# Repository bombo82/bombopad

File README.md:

# BomboPad

BomboPad is an open-source, versatile 12-key macropad featuring dual rotary encoders and display support. Designed with
a focus on flexibility, it supports both wired and wireless configurations.

This repository contains the hardware design files, including electrical schematics and PCB layouts.

## Key Features

The current hardware version (**v0.3**) includes:

- **12 keys**: Designed for Kailh Choc v1 low-profile switches.
- **Dual Rotary Encoders**: Supports EC11 or EVQWGD001 encoders.
- **Display Support**: Compatible with SSD1306 128x32 OLED or Nice!View displays.
- **Microcontroller Compatibility**:
    - **Pro Micro** (or compatible) for wired builds.
        - **ATmega32U4**: Fully tested and regularly used.
        - **RP2040**: Functionality verified, but not exhaustively tested.
    - **Nice!Nano** (or compatible) for wireless Bluetooth builds.
- **Battery Management**: Optional Li-Po battery and dedicated power switch for wireless operation.

## Getting Started (v0.3)

To build your own BomboPad, follow these steps:

### Hardware Requirements

- **PCB**: You can order the PCB using the provided [Gerber files](./gerbers/v0.3).
- **Components**: Refer to the **[Bill of Materials (BOM)](./schematics/v0.3/BOM.md)** for a complete list of required
  parts (switches, encoders, diodes, etc.).
- **Microcontroller**: Pro Micro (ATmega32U4 or RP2040) or Nice!Nano compatible.

### Assembly

The electrical schematics and PCB layout files are available in the **[schematics/](./schematics/v0.3)** directory (
KiCad format).

### Firmware

Choose the firmware that best fits your needs:

- **[QMK Firmware](https://github.com/bombo82/qmk_firmware/blob/bombopad/keyboards/handwired/bombopad/readme.md)**: Best
  for wired builds using a Pro Micro.
- **[VIAL Firmware](https://github.com/bombo82/vial-qmk/blob/bombopad/keyboards/handwired/bombopad/readme.md)**: Best
  for wired builds using a Pro Micro. Supports advanced features using VIAL for real-time configuration. See
  the firmware dedicate [release page](https://github.com/bombo82/vial-qmk/releases) for pre-compiled binaries.
- **[ZMK Firmware](https://github.com/bombo82/zmk-bombopad)**: Recommended for wireless builds using a Nice!Nano.

## Project Structure

- **`gerbers/`**: Production-ready Gerber files for PCB manufacturing.
- **`schematics/`**: KiCad project files, including schematics and PCB layout.
- **`BOM.md`**: Detailed Bill of Materials for the current hardware version.

## Version History

Summary of hardware evolution:

- **v0.3 (current)**
    - First version with PCB
    - Wired build using ProMicro compatible microcontroller with QMK or VIAL firmware
    - Wireless build using Nice!Nano compatible microcontroller with ZMK firmware
    - Kailh Choc v1 low-profile switch
    - EC11 rotary encoders or EVQWGD001 encoders
    - Optional display: SSD1306 128x32 on ProMicro microcontroller or Nice!View on Nice!Nano
    - Optional Lipo battery and power switch, depends on microcontroller capabilities
- **v0.2 (not compatible with QMK)**
    - Prototype on a solderless breadboard and a stripboard
    - Use expensive microcontroller and display
    - Bluetooth module and battery management module are integrate inside microcontroller
    - Shares the switch and encoders stripboard with v0.0
    - Disassembled to reuse some parts (microcontroller and display) to my own build of v0.3
- **v0.1 (never built)**
    - Scrapped at the design stage and never built
- **v0.0**
    - Initial prototype on a solderless breadboard and a stripboard
    - Low cost compoments
    - MX switch, EC11 rotary encoders, SSD1306 OLED 128x64 Pixel I2C
    - External HC-06 Bluetooth serial UART module

## Help & Contributions

Bug reports, suggestions, and contributions are welcome! Please
use [GitHub Issues](https://github.com/bombo82/bombopad/issues)
and [Discussions](https://github.com/bombo82/bombopad/discussions) for any feedback.

## Authors

- **Gianni Bombelli (bombo82)** - [GitHub Profile](https://github.com/bombo82)

## Licenses

Documentation are licensed under GNU Free Documentation License as published by the Free Software Foundation, either
version 1.3 of the License, or (at your option) any later version.

Source code are licensed under GNU General Public License as published by the Free Software Foundation, either version 3
of the License, or (at your option) any later version.

Hardware design and all related things are licensed under CERN Open Hardware Licence as published by the CERN, either
version 2 of the Licence, or (at your option) any later version.

## License Disclaimer

Copyright (C) 2024-2025 Gianni Bombelli <bombo82@giannibombelli.it>

Permission is granted to copy, distribute and/or modify this document
under the terms of the GNU Free Documentation License, Version 1.3
or any later version published by the Free Software Foundation;
with no Invariant Sections, no Front-Cover Texts, and no Back-Cover Texts.

You should have received a copy of the GNU Free Documentation License
along with this program. If not, see <https://www.gnu.org/licenses/fdl-1.3.html>.

## Acknowledgements

Special thanks to [Arialdo](https://github.com/arialdomartini) for introducing me to the world of custom mechanical
keyboards.

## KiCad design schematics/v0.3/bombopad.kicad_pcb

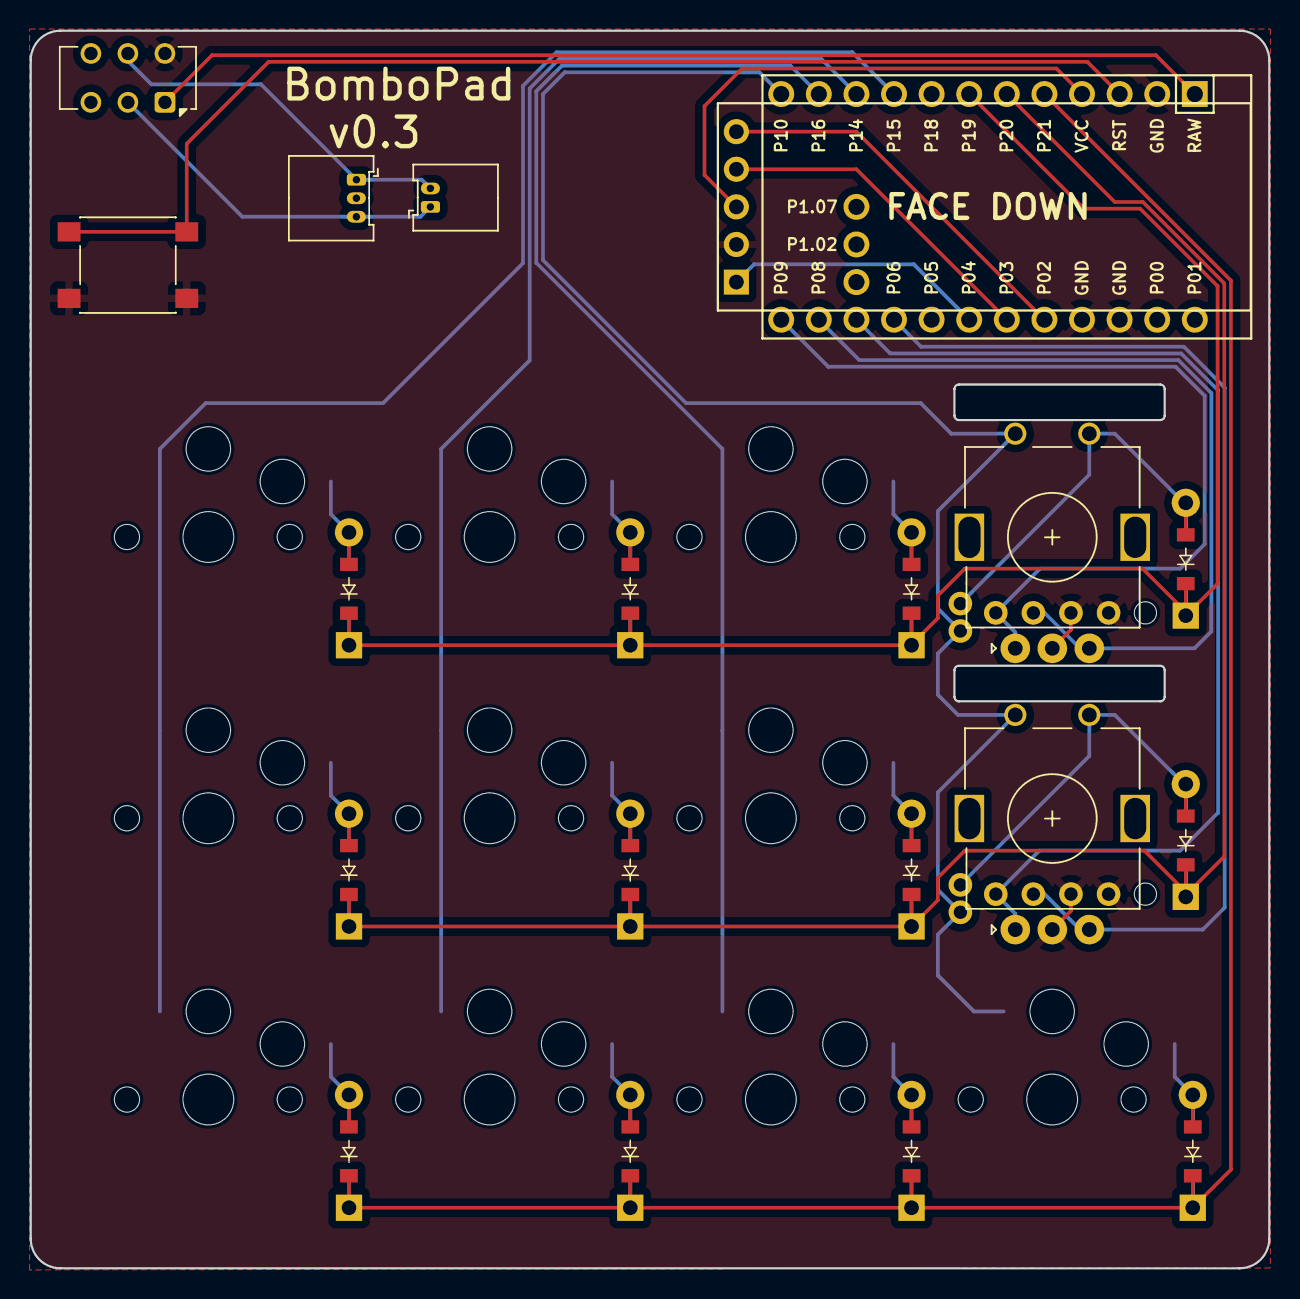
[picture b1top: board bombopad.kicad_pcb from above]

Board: 2 copper layers, 83.7 x 83.6 mm, 32 parts (0 on the bottom side), 32 nets.

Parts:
D1, D2, D3, D4, D5, D6, D7, D8, D9, D10, D11, D12: ComboDiode
J1: Conn_01x02; Molex_PicoBlade_53048-0210_1x02_P1.25mm_Horizontal
J2: Conn_01x03; Molex_PicoBlade_53048-0310_1x03_P1.25mm_Horizontal
MCU1: ProMicro
Nice!View1: niceview_headers
ROL1, ROL2: RollerEncoder_Panasonic_EVQWGD001
ROT1, ROT2: rotary_encoder
S1, S2, S3, S4, S5, S6, S7, S8, S9, S10: PG1350
S13: SW_Push_Dual_x2; SW_Push_1P1T_NO_6x6mm_H9.5mm
SW15: SW_DPDT_x2; SW_CK_JS202011AQN_DPDT_Angled

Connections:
+BATT: J1.1, J2.3, SW15.2 (B)
-BATT: J1.2, J2.1, SW15.5 (B)
GND: MCU1.2, MCU1.15, MCU1.16, Nice!View1.2, ROL1.C, ROL1.D, ROL2.C, ROL2.D, ROT1.C, ROT2.C, S13.1 (C), SW15.6 (C)
P2: MCU1.17, Nice!View1.5
P3: MCU1.18, Nice!View1.4
P4: MCU1.19, Nice!View1.1
P6: MCU1.21, ROL2.B, ROT2.B
P7: MCU1.22, ROL2.A, ROT2.A
P8: MCU1.23, ROL1.B, ROT1.B
P9: MCU1.24, ROL1.A, ROT1.A
P10: MCU1.12, ROL1.S1, ROL2.S1, ROT1.1, ROT2.1, S10.1
P14: MCU1.10, S4.1, S5.1, S6.1
P15: MCU1.9, S1.1, S2.1, S3.1
P16: MCU1.11, S7.1, S8.1, S9.1
P19: D3.1, D6.1, D9.1, D12.1, MCU1.7
P20: D2.1, D5.1, D8.1, D11.1, MCU1.6
P21: D1.1, D4.1, D7.1, D10.1, MCU1.5
RAW: MCU1.1, SW15.1 (A)
RST: MCU1.3, S13.2 (D)
VCC: MCU1.4, Nice!View1.3
index_bottom: D7.2, S7.2
index_home: D8.2, S8.2
index_top: D9.2, S9.2
middle_bottom: D4.2, S4.2
middle_home: D5.2, S5.2
middle_top: D6.2, S6.2
ring_bottom: D1.2, S1.2
ring_home: D2.2, S2.2
ring_top: D3.2, S3.2
thumb_bottom: D10.2, S10.2
thumb_home: D11.2, ROL2.S2, ROT2.2
thumb_top: D12.2, ROL1.S2, ROT1.2

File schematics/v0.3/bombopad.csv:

"Id";"Designator";"Footprint";"Quantity";"Designation";"Supplier and ref";
1;"D1,D2,D3,D4,D5,D6,D7,D8,D9,D10,D11,D12";"ComboDiode";12;"";;;
2;"J1";"Molex_PicoBlade_53048-0210_1x02_P1.25mm_Horizontal";1;"Conn_01x02";;;
3;"J2";"Molex_PicoBlade_53048-0310_1x03_P1.25mm_Horizontal";1;"Conn_01x03";;;
4;"MCU1";"ProMicro";1;"";;;
5;"Nice!View1";"niceview_headers";1;"";;;
6;"ROL1,ROL2";"RollerEncoder_Panasonic_EVQWGD001";2;"";;;
7;"ROT1,ROT2";"rotary_encoder";2;"";;;
8;"S13";SW_Push_1P1T_NO_6x6mm_H9.5mm;1;"SW_Push_Dual_x2";;;
9;"S1,S2,S3,S4,S5,S6,S7,S8,S9,S10";"PG1350";10;"";;;
10;"SW15";"SW_CK_JS202011AQN_DPDT_Angled";1;"SW_DPDT_x2";;;

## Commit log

2024-10-12 final v0.3 schematics and gerber files
2024-10-12 add readme file
2024-10-13 use of plular in the name of directories
2024-10-13 add empty directory to maintain the structure
2025-12-29 add BOM and CSV files for BomboPad v0.3 schematics
2025-12-29 add license notice
2025-12-29 Update README with detailed project description and documentation links
2025-12-29 add schematics and project files for BomboPad v0.1 (only for historical reasons)
2025-12-29 fix typo
2025-12-29 add schematics (pdf format) for BomboPad v0.0 (only for historical reasons)
2025-12-29 Correct capitalization of "Nice!Nano," "Nice!View," and "Kailh Choc v1" in documentation.
2025-12-30 Update BOM and documentation: clarify MCU compatibility and other minor changes.
2026-01-01 Refine BomboPad documentation and update microcontroller details

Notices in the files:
schematics/v0.3/bombopad.kicad_pcb:
of the CERN-OHL-S v2 (https://ohwr.org/cern_ohl_s_v2.txt).
This source describes Open Hardware and is licensed under the CERN-OHL-S v2 or
